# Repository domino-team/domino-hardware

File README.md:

This repository contains the Domino.IO hardware design files.

For further information, please check http://domino.io/

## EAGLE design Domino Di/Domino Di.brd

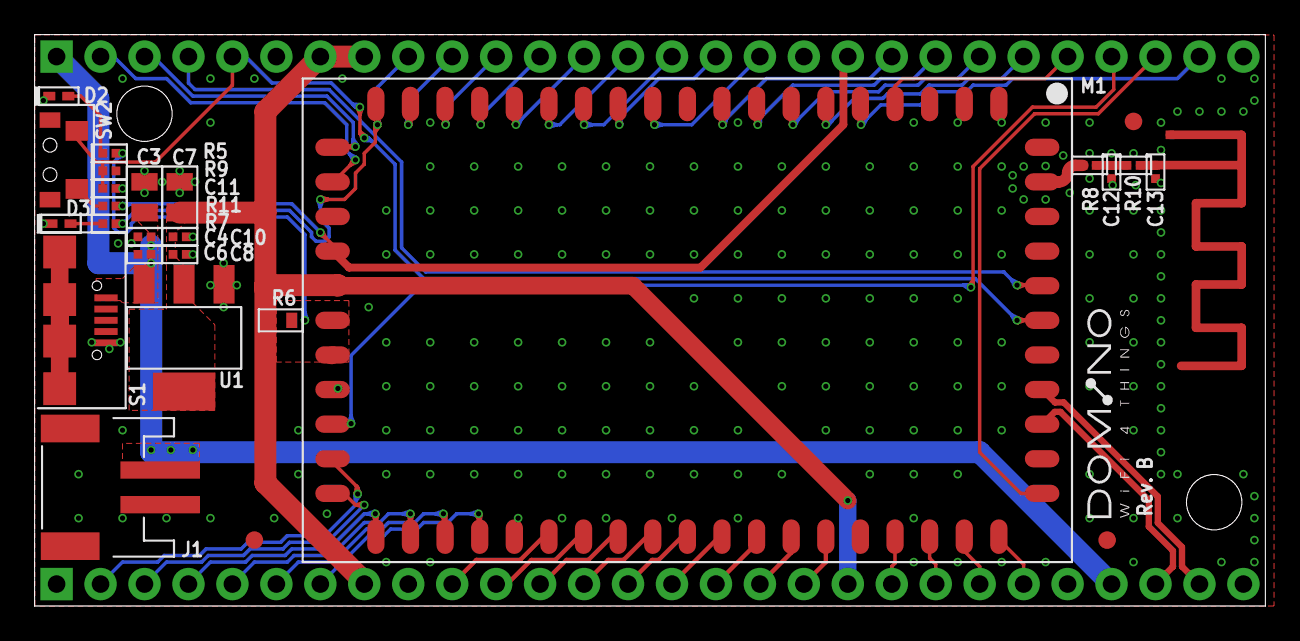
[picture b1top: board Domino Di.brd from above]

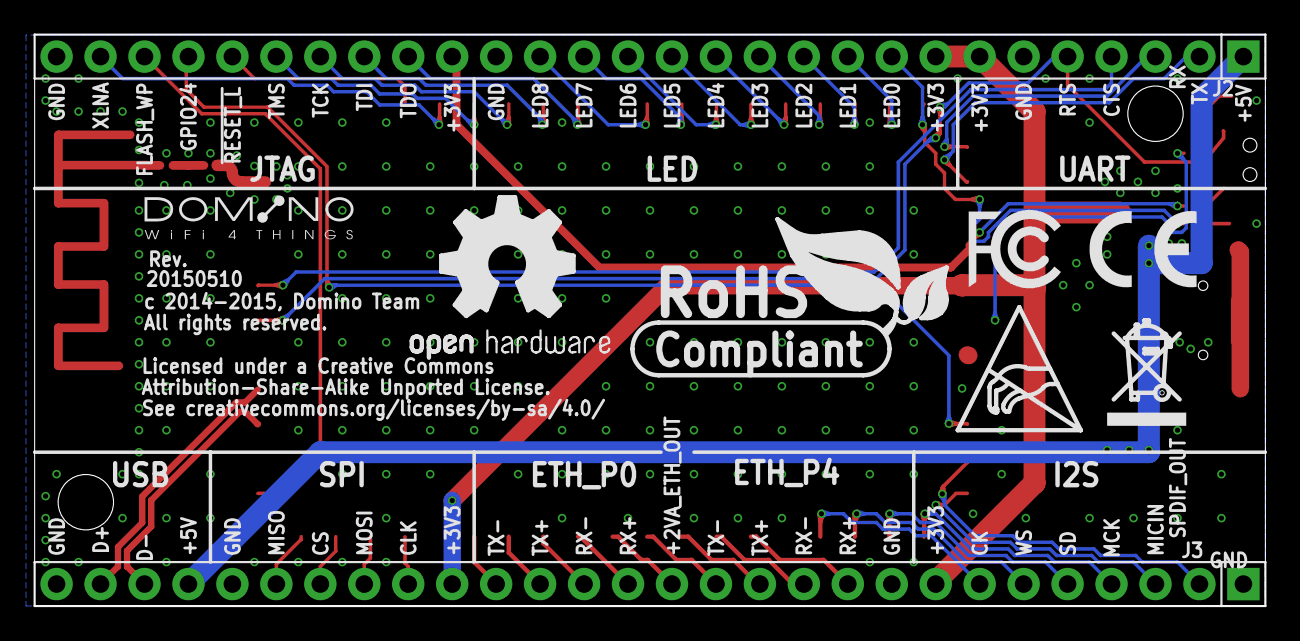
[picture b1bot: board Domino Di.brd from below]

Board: 2 copper layers, 71.1 x 33.0 mm, 41 parts (9 on the bottom side), 53 nets.

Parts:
A1: RF_ANT1
C3, C7: 22u; C0805
C4, C8: 10p; C0402
C6, C10: 100n; C0402
C11: 10n; C0402
C12, C13: DNP; C0402
CC-BY-SA: CC-BY-SA_LOGO
D2: RED; LED0402
D3: BLUE; LED0402
DRILEGEND: DRILEGEND
F1, F2, F3: FIDUCIAL
J1: LiPo Battery; S2B-PH-SM4-TB
J2, J3: MH28-1; MH28-1-0.1
M1: DOMINO
R5, R7: 270R; R0402
R6: 0R; R0603
R8, R10: 0R; R0402
R9: 10k; R0402
R11: 1k; R0402
S1: USB_MR5-001; USB-MR5-001
SW2: IT-1210
U1: AMS1117-3.3; SOT223
U$6, U$8: DOMINO_LOGO_SMALL
U$28: A5L-LOC
U$36: ESD_LOGO
U$38: OPEN_HARDWARE_LOGO
U$39: RECYCLE_BIN_LOGO
U$40: ROHS_LOGO
U$41: CE_LOGO_SMALL
U$42: FCC_LOGO_SMALL
W1: DOMINO_LOGO

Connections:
!RESET_L: J2.24, M1.4
+2V5: J2.19, M1.23, R11.2
+2VA_ETH_OUT: J3.14, M1.40
+3.3VD_IN: M1.25, M1.26, R5.2, R6.2
+3V3: C7.1, C8.1, C10.1, J2.7, J2.8, J3.8, J3.19, M1.24, R6.1, U1.2, U1.4
+5V: C3.1, C4.1, C6.1, J1.2, J2.1, J3.25, S1.1, U1.3
ANT0: M1.59, R8.1
ANT0_50R: A1.FEED, C13.1, R10.2
ANT0_EXT: C12.1, R8.2, R10.1
BLUE_LED: D3.2, R7.1
FLASH_WP: J2.26, M1.50
GND: A1.GND, C3.2, C4.2, C6.2, C7.2, C8.2, C10.2, C11.2, C12.2, C13.2, D2.1, D3.1, J1.1, J2.6, J2.18, J2.28, J3.1, J3.9, J3.24, J3.28, M1.1, M1.2, M1.3, M1.10, M1.22, M1.27, M1.35, M1.45, M1.51, M1.54, M1.57, M1.58, M1.60, R9.1, S1.5, S1.SH$1, S1.SH$2, S1.SH$3, S1.SH$4, SW2.SH$1, SW2.SH$2, U1.1
GPIO24: J2.25, M1.28
I2S_CK: J3.7, M1.34
I2S_MCK: J3.4, M1.31
I2S_MICIN: J3.3, M1.30
I2S_SD: J3.5, M1.32
I2S_WS: J3.6, M1.33
JTAG_TCK: J2.22, M1.7
JTAG_TDI: J2.21, M1.8
JTAG_TDO: J2.20, M1.9
JTAG_TMS: J2.23, M1.6
JUMPSTART: R11.1, SW2.1
LED0: J2.9, M1.19, R7.2
LED1: J2.10, M1.18
LED2: J2.11, M1.17
LED3: J2.12, M1.16
LED4: J2.13, M1.15
LED5: J2.14, M1.14
LED6: J2.15, M1.13
LED7: J2.16, M1.12
LED8: J2.17, M1.11
unnamed: D2.2, R5.1
P0_RX+: J3.15, M1.41
P0_RX-: J3.16, M1.42
P0_TX+: J3.17, M1.43
P0_TX-: J3.18, M1.44
P4_RX+: J3.10, M1.36
P4_RX-: J3.11, M1.37
P4_TX+: J3.12, M1.38
P4_TX-: J3.13, M1.39
SPDIF_OUT: J3.2, M1.29
SPI_CLK: J3.20, M1.46
SPI_CS: J3.22, M1.48
SPI_MISO: J3.23, M1.49
SPI_MOSI: J3.21, M1.47
UART_CTS: J2.4, M1.56
UART_RTS: C11.1, J2.5, M1.55, R9.2, SW2.2
UART_RX: J2.3, M1.20
UART_TX: J2.2, M1.21
USB_N: J3.26, M1.52
USB_P: J3.27, M1.53
XLNA: J2.27, M1.5

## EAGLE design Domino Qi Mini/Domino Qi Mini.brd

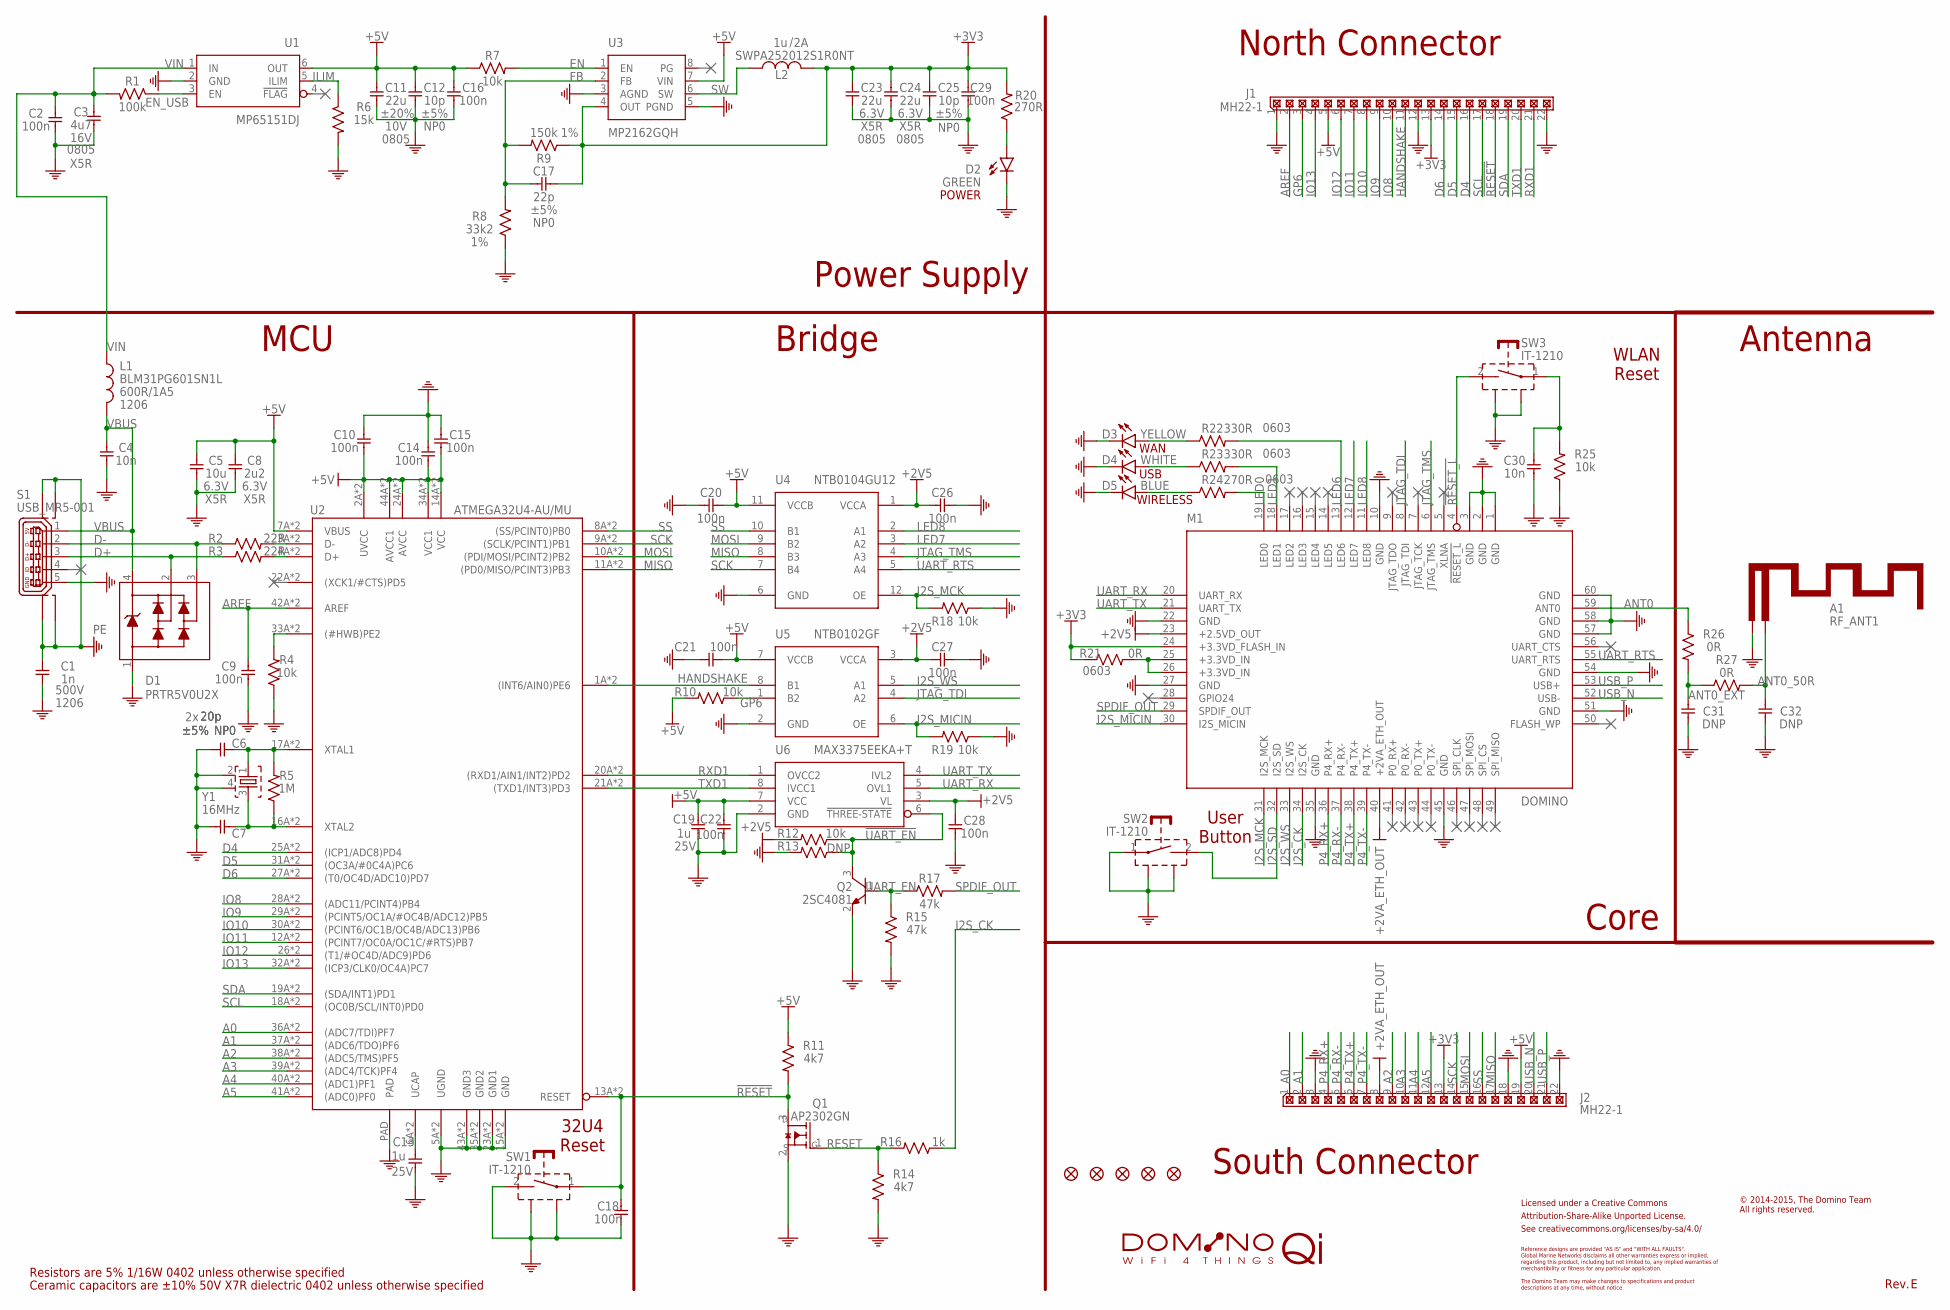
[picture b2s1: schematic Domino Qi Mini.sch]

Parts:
A1: RF_ANT1; PARTNO RF_ANT1
C1: 1n; C1206; PARTNO C1206_1n_X7R_10%_CER_500V
C2, C9, C10, C14, C15, C16, C18, C20, C21, C22, C26, C27, C28, C29: 100n; C0402; PARTNO C0402_100n_X7R_10%_CER_50V
C3: 4u7; C0805; PARTNO C0805_4u7_X5R_10%_CER_16V
C4, C30: 10n; C0402; PARTNO C0402_10n_X7R_10%_CER_50V
C5: 10u; C0402; PARTNO C0402_10u_X5R_10%_CER_6V3
C6, C7: 20p; C0402; PARTNO C0402_20p_NP0_5%_CER_50V
C8: 2u2; C0805; PARTNO C0402_2u2_X5R_10%_CER_6V3
C11: 22u; C0805; PARTNO C1206_22u_X7R_20%_CER_10V
C12, C25: 10p; C0402; PARTNO C0402_10p_NP0_5%_CER_50V
C13, C19: 1u; C0402; PARTNO C0402_1u_X7R_10%_CER_25V
C17: 22p; C0402; PARTNO C0402_22p_NP0_5%_CER_50V
C23, C24: 22u; C0805; PARTNO C0805_22u_X5R_20%_CER_6V3
C31, C32: DNP; C0402; PARTNO C0402_DNP
CC-BY-SA: CC-BY-SA_LOGO
D1: PRTR5V0U2X; SOT143B; PARTNO PRTR5V0U2X
D2: GREEN; LED0402; PARTNO LED0603-GREEN
D3: YELLOW; LED0402; PARTNO LED0603-YELLOW
D4: WHITE; LED0402; PARTNO LED0603-WHITE
D5: BLUE; LED0402; PARTNO LED0603-BLUE
F1, F2, F3, F4, F5: FIDUCIAL
J1, J2: MH22-1; MH22-1-0.1; PARTNO MH22-1-0.1
L1: BLM31PG601SN1L; FB1206; PARTNO BLM31PG601SN1L
L2: SWPA252012S1R0NT; SWPA252012S; PARTNO SWPA252012SMT
M1: DOMINO; PARTNO DOMINO-CORE
Q1: AP2302GN; SOT23-3; PARTNO AP2302GN
Q2: 2SC4081; SOT323; PARTNO 2SC4081
R1: 100k; R0402; PARTNO R0402_100k_5%_62.5mW
R2, R3: 22R; R0402; PARTNO R0402_22R_5%_62.5mW
R4, R7, R10, R12, R13, R18, R19, R25: 10k; R0402; PARTNO R0402_10k_5%_62.5mW
R5: 1M; R0402; PARTNO R0402_1M_5%_62.5mW
R6: 15k; R0402; PARTNO R0402_15k_5%_62.5mW
R8: 33k2; R0402; PARTNO R0402_33k2_1%_62.5mW
R9: 150k; R0402; PARTNO R0402_150k_1%_62.5mW
R11, R14: 4k7; R0402; PARTNO R0402_4k7_5%_62.5mW
R15, R17: 47k; R0402; PARTNO R0402_47k_5%_62.5mW
R16: 1k; R0402; PARTNO R0402_1k_5%_62.5mW
R20: 270R; R0402; PARTNO R0402_270R_5%_62.5mW
R21: 0R; R0603; PARTNO R0603_0R_5%_125mW
R22, R23: 330R; R0603; PARTNO R0603_330R_5%_125mW
R24: 270R; R0603; PARTNO R0603_270R_5%_125mW
R26, R27: 0R; R0402; PARTNO R0402_0R_5%_62.5mW
S1: USB_MR5-001; USB-MR5-001; PARTNO USB MR5-003A
SW1, SW2, SW3: IT-1210; PARTNO IT-1210
U1: MP65151DJ; SOT23-6; PARTNO MP65151DJ
U2: ATMEGA32U4-AU/MU; ATMEGA32U4_DUAL_FOOTPRINT; PARTNO ATMEGA32U4-MU
U3: MP2162GQH; QFN-8_2X1.5; PARTNO MP2162GQH
U4: NTB0104GU12; XQFN-12; PARTNO NTB0104GU12
U5: NTB0102GF; SOT1089; PARTNO NTB0102GF
U6: MAX3375EEKA+T; SOT23-8; PARTNO MAX3375EEKA+T
W1: DOMINO_QI_LOGO
Y1: 16MHz; CRYSTAL_32X25; PARTNO CRYSTAL_16MHZ_32X25_2SH_12PF_30PPM

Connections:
!RESET: C18.1, J1.18, Q1.3 (D), R11.2, SW1.1, U2.13A (RESET), U2.13M (RESET)
!RESET_L: M1.4 (!RESET_L), SW3.2
!UART_EN: Q2.3 (C), R12.1, R13.1, U6.6 (!THREE-STATE)
+2V5: C26.1, C27.1, C28.1, M1.23 (+2.5VD_OUT), R12.2, U4.1 (VCCA), U5.3 (VCCA), U6.3 (VL)
+2VA_ETH_OUT: J2.8, M1.40 (+2VA_ETH_OUT)
+3.3VD_IN: M1.25 (+3.3VD_IN), M1.26 (+3.3VD_IN), R21.2
+3V3: C17.2, C23.1, C24.1, C25.1, C29.1, J1.13, J2.13, L2.2, M1.24 (+3.3VD_FLASH_IN), R9.1, R20.2, R21.1, U3.4 (OUT)
+5V: C5.1, C8.1, C10.1, C11.1, C12.1, C14.1, C15.1, C16.1, C19.2, C20.1, C21.1, C22.1, J1.5, J2.19, R7.1, R10.2, R11.1, U1.6 (OUT), U2.2A (UVCC), U2.2M (UVCC), U2.7A (VBUS), U2.7M (VBUS), U2.14A (VCC), U2.14M (VCC), U2.24A (AVCC), U2.24M (AVCC), U2.34A (VCC1), U2.34M (VCC1), U2.44A (AVCC1), U2.44M (AVCC1), U3.7 (VIN), U4.11 (VCCB), U5.7 (VCCB), U6.7 (VCC)
A0: J2.1, U2.36A ((ADC7/TDI)PF7), U2.36M ((ADC7/TDI)PF7)
A1: J2.2, U2.37A ((ADC6/TDO)PF6), U2.37M ((ADC6/TDO)PF6)
A2: J2.9, U2.38A ((ADC5/TMS)PF5), U2.38M ((ADC5/TMS)PF5)
A3: J2.10, U2.39A ((ADC4/TCK)PF4), U2.39M ((ADC4/TCK)PF4)
A4: J2.11, U2.40A ((ADC1)PF1), U2.40M ((ADC1)PF1)
A5: J2.12, U2.41A ((ADC0)PF0), U2.41M ((ADC0)PF0)
ANT0: M1.59 (ANT0), R26.1
ANT0_50R: A1.FEED, C32.1, R27.2
ANT0_EXT: C31.1, R26.2, R27.1
AREF: C9.1, J1.2, U2.42A (AREF), U2.42M (AREF)
BLUE_LED: D5.2 (A), R24.1
BLUE_LED1: D4.2 (A), R23.1
BLUE_LED2: D3.2 (A), R22.1
D4: J1.16, U2.25A ((ICP1/ADC8)PD4), U2.25M ((ICP1/ADC8)PD4)
D5: J1.15, U2.31A ((OC3A/#0C4A)PC6), U2.31M ((OC3A/#0C4A)PC6)
D6: J1.14, U2.27A ((T0/OC4D/ADC10)PD7), U2.27M ((T0/OC4D/ADC10)PD7)
D+: D1.2, R3.1, S1.3
D-: D1.3, R2.1, S1.2
EN: R7.2, U3.1 (EN)
EN_USB: R1.1, U1.3 (EN)
FB: C17.1, R8.2, R9.2, U3.2 (FB)
GND: A1.GND, C1.2, C2.2, C3.2, C4.2, C5.2, C6.1, C7.1, C8.2, C9.2, C10.2, C11.2, C12.2, C13.1, C14.2, C15.2, C16.2, C18.2, C19.1, C20.2, C21.2, C22.2, C23.2, C24.2, C25.2, C26.2, C27.2, C28.2, C29.2, C30.2, C31.2, C32.2, D1.1, D2.1 (C), D3.1 (C), D4.1 (C), D5.1 (C), J1.1, J1.12, J1.22, J2.3, J2.18, J2.22, M1.1 (GND), M1.2 (GND), M1.3 (GND), M1.10 (GND), M1.22 (GND), M1.27 (GND), M1.35 (GND), M1.45 (GND), M1.51 (GND), M1.54 (GND), M1.57 (GND), M1.58 (GND), M1.60 (GND), Q1.2 (S), Q2.2 (E), R4.1, R6.2, R8.1, R13.2, R14.2, R15.2, R18.1, R19.1, R25.1, S1.5, SW1.2, SW1.SH$1, SW1.SH$2, SW2.1, SW2.SH$1, SW2.SH$2, SW3.SH$1, SW3.SH$2, U1.2 (GND), U2.5A (UGND), U2.5M (UGND), U2.15A (GND), U2.15M (GND), U2.23A (GND1), U2.23M (GND1), U2.35A (GND2), U2.35M (GND2), U2.43A (GND3), U2.43M (GND3), U2.PAD, U3.3 (AGND), U3.5 (PGND), U4.6 (GND), U5.2 (GND), U6.2 (GND), Y1.2, Y1.4
GP6: J1.3, R10.1, U5.1 (B2)
HANDSHAKE: J1.11, U2.1A ((INT6/AIN0)PE6), U2.1M ((INT6/AIN0)PE6), U5.8 (B1)
I2S_CK: M1.34 (I2S_CK), R16.1
I2S_MCK: M1.31 (I2S_MCK), R18.2, U4.12 (OE)
I2S_MICIN: M1.30 (I2S_MICIN), R19.2, U5.6 (OE)
I2S_SD: M1.32 (I2S_SD), SW2.2
I2S_WS: M1.33 (I2S_WS), U5.5 (A1)
ILIM: R6.1, U1.5 (ILIM)
IO8: J1.10, U2.28A ((ADC11/PCINT4)PB4), U2.28M ((ADC11/PCINT4)PB4)
IO9: J1.9, U2.29A ((PCINT5/OC1A/#OC4B/ADC12)PB5), U2.29M ((PCINT5/OC1A/#OC4B/ADC12)PB5)
IO10: J1.8, U2.30A ((PCINT6/OC1B/OC4B/ADC13)PB6), U2.30M ((PCINT6/OC1B/OC4B/ADC13)PB6)
IO11: J1.7, U2.12A ((PCINT7/OC0A/OC1C/#RTS)PB7), U2.12M ((PCINT7/OC0A/OC1C/#RTS)PB7)
IO12: J1.6, U2.26 ((T1/#OC4D/ADC9)PD6), U2.26M ((T1/#OC4D/ADC9)PD6)
IO13: J1.4, U2.32A ((ICP3/CLK0/OC4A)PC7), U2.32M ((ICP3/CLK0/OC4A)PC7)
JTAG_TDI: M1.8 (JTAG_TDI), U5.4 (A2)
JTAG_TMS: M1.6 (JTAG_TMS), U4.4 (A3)
LED0: M1.19 (LED0), R24.2
LED1: M1.18 (LED1), R23.2
LED6: M1.13 (LED6), R22.2
LED7: M1.12 (LED7), U4.3 (A2)
LED8: M1.11 (LED8), U4.2 (A1)
MISO: J2.17, U2.11A ((PD0/MISO/PCINT3)PB3), U2.11M ((PD0/MISO/PCINT3)PB3), U4.8 (B3)
MOSI: J2.15, U2.10A ((PDI/MOSI/PCINT2)PB2), U2.10M ((PDI/MOSI/PCINT2)PB2), U4.9 (B2)
unnamed: R2.2, U2.3A (D-), U2.3M (D-)
unnamed: R4.2, U2.33A ((#HWB)PE2), U2.33M ((#HWB)PE2)
unnamed: R3.2, U2.4A (D+), U2.4M (D+)
P4_RX+: J2.4, M1.36 (P4_RX+)
P4_RX-: J2.5, M1.37 (P4_RX-)
P4_TX+: J2.6, M1.38 (P4_TX+)
P4_TX-: J2.7, M1.39 (P4_TX-)
PE: C1.1, S1.SH$1 (M0), S1.SH$2 (M1), S1.SH$3 (M2), S1.SH$4 (M3)
POWER_LED: D2.2 (A), R20.1
RESET: Q1.1 (G), R14.1, R16.2
RESET_SWITCH: C30.1, R25.2, SW3.1
RXD1: J1.21, U2.20A ((RXD1/AIN1/INT2)PD2), U2.20M ((RXD1/AIN1/INT2)PD2), U6.1 (OVCC2)
SCK: J2.14, U2.9A ((SCLK/PCINT1)PB1), U2.9M ((SCLK/PCINT1)PB1), U4.7 (B4)
SCL: J1.17, U2.18A ((OC0B/SCL/INT0)PD0), U2.18M ((OC0B/SCL/INT0)PD0)
SDA: J1.19, U2.19A ((SDA/INT1)PD1), U2.19M ((SDA/INT1)PD1)
SPDIF_OUT: M1.29 (SPDIF_OUT), R17.2
SS: J2.16, U2.8A ((SS/PCINT0)PB0), U2.8M ((SS/PCINT0)PB0), U4.10 (B1)
SW: L2.1, U3.6 (SW)
TXD1: J1.20, U2.21A ((TXD1/INT3)PD3), U2.21M ((TXD1/INT3)PD3), U6.8 (IVCC1)
UART_EN: Q2.1 (B), R15.1, R17.1
UART_RTS: M1.55 (UART_RTS), U4.5 (A4)
UART_RX: M1.20 (UART_RX), U6.5 (OVL1)
UART_TX: M1.21 (UART_TX), U6.4 (IVL2)
UCAP: C13.2, U2.6A (UCAP), U2.6M (UCAP)
USB_N: J2.20, M1.52 (USB-)
USB_P: J2.21, M1.53 (USB+)
VBUS: C4.1, D1.4, L1.2, S1.1
VIN: C2.1, C3.1, L1.1, R1.2, U1.1 (IN)
XTAL1: C6.2, R5.2, U2.17A (XTAL1), U2.17M (XTAL1), Y1.1
XTAL2: C7.2, R5.1, U2.16A (XTAL2), U2.16M (XTAL2), Y1.3

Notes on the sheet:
Power Supply
North Connector
South Connector
Antenna
Core
MCU
Ceramic capacitors are ±10% 50V X7R dielectric 0402 unless otherwise specified
Resistors are 5% 1/16W 0402 unless otherwise specified
Licensed under a Creative Commons
Attribution-Share-Alike Unported License.
See creativecommons.org/licenses/by-sa/4.0/
Reference designs are provided "AS IS" and "WITH ALL FAULTS".
regarding this product, including but not limited to, any implied warranties of
The Domino Team may make changes to specifications and product
Global Marine Networks disclaims all other warranties express or implied,
merchantibility or fitness for any particular application.
descriptions at any time, without notice.
© 2014-2015, The Domino Team All rights reserved.
Rev.
WIRELESS
POWER
Bridge
32U4 Reset
USB
WAN
User Button
WLAN Reset

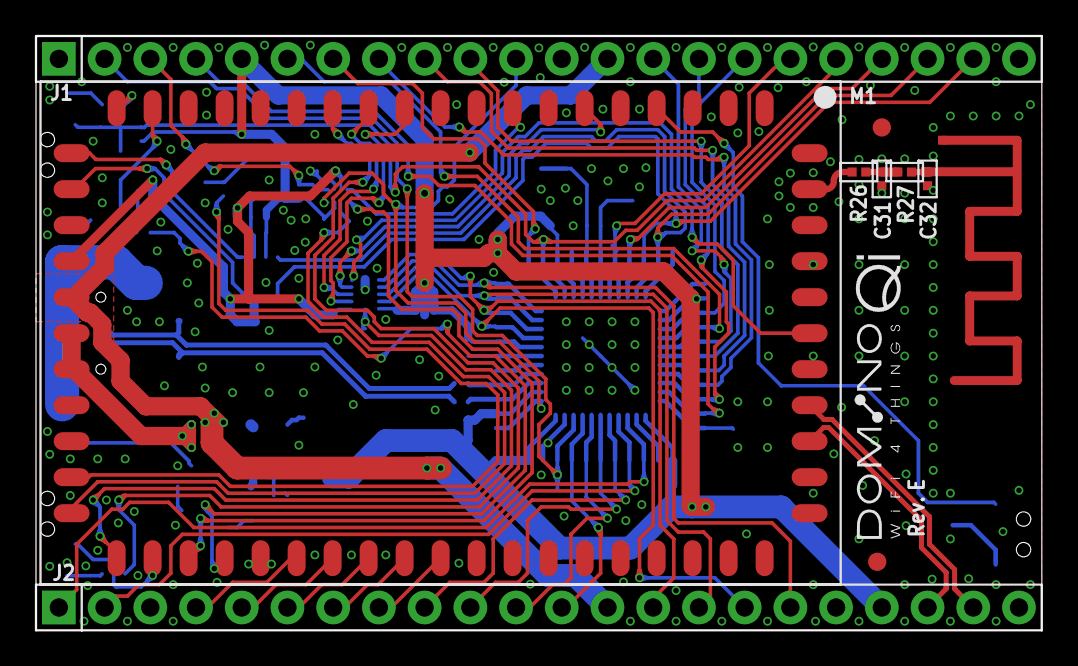
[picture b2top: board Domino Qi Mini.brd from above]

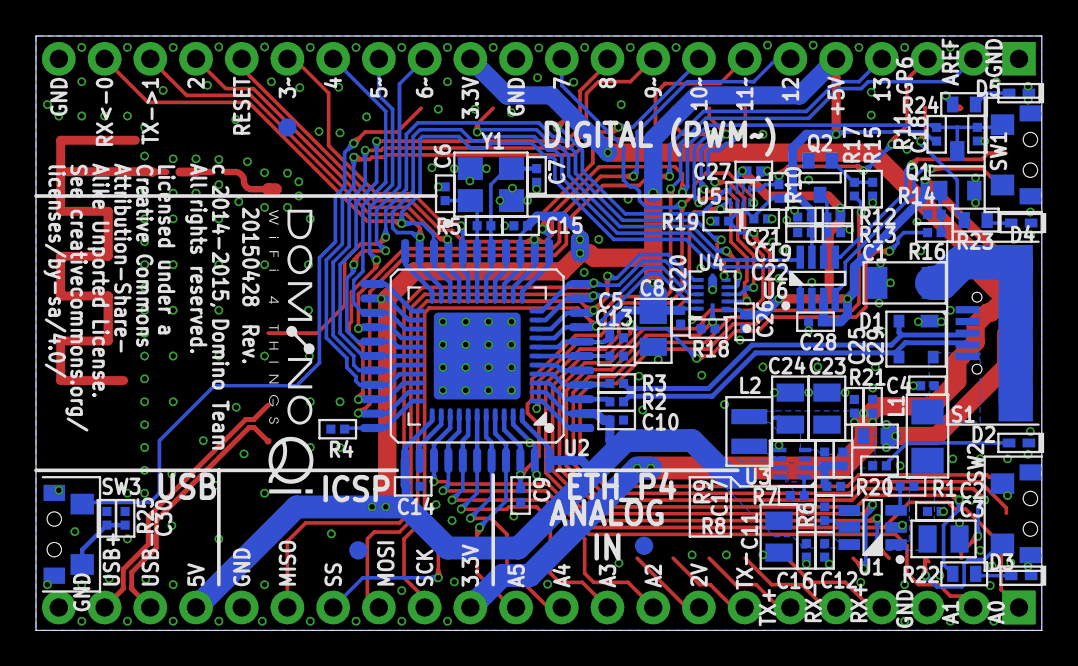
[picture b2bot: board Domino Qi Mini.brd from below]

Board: 4 copper layers, 55.9 x 33.0 mm, 94 parts (79 on the bottom side), 83 nets.

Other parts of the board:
DRILEGEND: DRILEGEND
U$3, U$5: DOMINO_QI_LOGO_SMALL
U$28: A5L-LOC

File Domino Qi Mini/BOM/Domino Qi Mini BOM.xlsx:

Item | Qty | Value | Manufacturer | Device | Package | Reference | Description | Remarks
1 | 1 | 1n | ANY | C1206_1n_X7R_10%_CER_500V | C1206 | C1 | CAP CER 1000PF 500V 10% X7R 1206
2 | 1 | 22u | ANY | C1206_22u_X7R_20%_CER_10V | C0805 | C11 | CAP CER 22UF 10V 20% X7R 1206
3 | 2 | 10p | ANY | C0402_10p_NP0_5%_CER_50V | C0402 | C12, C25 | CAP CER 10PF 50V 5% NP0 0402
4 | 2 | 1u | ANY | C0402_1u_X7R_10%_CER_25V | C0402 | C13, C19 | CAP CER 1UF 25V 10% X7R 0402
5 | 1 | 22p | ANY | C0402_22p_NP0_5%_CER_50V | C0402 | C17 | CAP CER 22PF 50V 5% NP0 0402
6 | 14 | 100n | ANY | C0402_100n_X7R_10%_CER_50V | C0402 | C2, C9, C10, C14, C15, C16, C18, C20, C21, C22, C26, C27, C28, C29 | CAP CER 0.1UF 50V 10% X7R 0402
7 | 2 | 22u | ANY | C0805_22u_X5R_20%_CER_6V3 | C0805 | C23, C24 | CAP CER 22UF 6.3V 20% X5R 0805
8 | 1 | 4u7 | ANY | C0805_4u7_X5R_10%_CER_16V | C0805 | C3 | CAP CER 4.7UF 16V 10% X5R 0805
9 | 0 | DNP | NONE | C0402_DNP | C0402 | C31(DNP), C32(DNP) | CAP DNP 0402
10 | 2 | 10n | ANY | C0402_10n_X7R_10%_CER_50V | C0402 | C4, C30 | CAP CER 10000PF 50V 10% X7R 0402
11 | 1 | 10u | ANY | C0402_10u_X5R_10%_CER_6V3 | C0402 | C5 | CAP CER 10UF 6.3V 10% X5R 0402
12 | 2 | 20p | ANY | C0402_20p_NP0_5%_CER_50V | C0402 | C6, C7 | CAP CER 20PF 50V 5% NP0 0402
13 | 1 | 2u2 | ANY | C0402_2u2_X5R_10%_CER_6V3 | C0805 | C8 | CAP CER 2.2UF 6.3V 20% X5R 0402
14 | 1 | PRTR5V0U2X | NXP | PRTR5V0U2X | SOT143B | D1 | TVS DIODE ARRAY 2CH 5V SOT143
15 | 1 | GREEN | ANY | LED0603-GREEN | LED0402 | D2 | LED GREEN CLEAR 0603 SMD
16 | 1 | YELLOW | ANY | LED0603-YELLOW | LED0402 | D3 | LED YELLOW CLEAR 0603 SMD
17 | 1 | WHITE | ANY | LED0603-WHITE | LED0402 | D4 | LED WHITE CLEAR 0603 SMD
18 | 1 | BLUE | ANY | LED0603-BLUE | LED0402 | D5 | LED BLUE CLEAR 0603 SMD
19 | 2 | MH22-1 | ANY | MH22-1-0.1 | MH22-1-0.1 | J1, J2 | CONN HEADER VERT .100 1ROW 22POS 10.5 TAIL 8.5 BODY 15AU
20 | 1 | BLM31PG601SN1L | MURATA | BLM31PG601SN1L | FB1206 | L1 | FERRITE CHIP 600 OHM 1500MA 1206
21 | 1 | SWPA252012S1R0NT | SUNLORD | SWPA252012SMT | SWPA252012S | L2 | INDUCTOR 1.2UH 2.0A SMD2.5 X 2.0 X 1.2
22 | 1 | DOMINO | GL-CONNECT | DOMINO-CORE | DOMINO | M1 | MOD AR9331 WIFI
23 | 1 | AP2302GN | ANPEC | AP2302GN | SOT23-3 | Q1 | MOSFET N-CH 20V 2.8A SOT-23
24 | 1 | 2SC4081 | ROHM SEMICONDUCTOR | 2SC4081 | SOT323 | Q2 | TRANS NPN 50V 0.15A SOT-323
25 | 1 | 100k | ANY | R0402_100k_5%_62.5mW | R0402 | R1 | RES 100K OHM 1/16W 5% 0402 SMD
26 | 2 | 4k7 | ANY | R0402_4k7_5%_62.5mW | R0402 | R11, R14 | RES 4.7K OHM 1/16W 5% 0402 SMD
27 | 2 | 47k | ANY | R0402_47k_5%_62.5mW | R0402 | R15, R17 | RES 47K OHM 1/16W 5% 0402 SMD
28 | 1 | 1k | ANY | R0402_1k_5%_62.5mW | R0402 | R16 | RES 1K OHM 1/16W 5% 0402 SMD
29 | 2 | 22R | ANY | R0402_22R_5%_62.5mW | R0402 | R2, R3 | RES 22 OHM 1/16W 5% 0402 SMD
30 | 1 | 270R | ANY | R0402_270R_5%_62.5mW | R0402 | R20 | RES 270 OHM 1/16W 5% 0402 SMD
31 | 1 | 0R | ANY | R0603_0R_5%_125mW | R0603 | R21 | RES 0.0 OHM 1/8W JUMP SMD 0603
32 | 2 | 330R | ANY | R0603_330R_5%_125mW | R0603 | R22, R23 | RES 330 OHM 1/8W 5% 0603 SMD
33 | 1 | 270R | ANY | R0603_270R_5%_125mW | R0603 | R24 | RES 270 OHM 1/8W 5% 0603 SMD
34 | 2 | 0R | ANY | R0402_0R_5%_62.5mW | R0402 | R26, R27 | RES 0.0 OHM 1/16W JUMP 0402 SMD
35 | 7 | 10k | ANY | R0402_10k_5%_62.5mW | R0402 | R4, R7, R10, R12, R13(DNP), R18, R19, R25 | RES 10K OHM 1/16W 5% 0402 SMD
36 | 1 | 1M | ANY | R0402_1M_5%_62.5mW | R0402 | R5 | RES 1M OHM 1/16W 0402 SMD
37 | 1 | 15k | ANY | R0402_15k_5%_62.5mW | R0402 | R6 | RES 15K OHM 1/16W 5% 0402 SMD
38 | 1 | 33k2 | ANY | R0402_33k2_1%_62.5mW | R0402 | R8 | RES 33.2K OHM 1/16W 1% 0402 SMD
39 | 1 | 150k | ANY | R0402_150k_1%_62.5mW | R0402 | R9 | RES 150K OHM 1/16W 1% 0402 SMD
40 | 1 | USB_MR5-001 | SZJUSTWELL ELECTRONICS | USB MR5-003A | USB-MR5-001 | S1 | CONN USB MICRO B RECPT SMT R/A
41 | 3 | IT-1210 | SZJUSTWELL ELECTRONICS | IT-1210 | IT-1210 | SW1, SW2, SW3 | SWITCH TACTILE SPST-NO 0.05A 12V
42 | 1 | MP65151DJ | MONOLITHIC POWER | MP65151DJ | SOT23-6 | U1 | IC POWER SWITCH 1.7A SOT23-6
43 | 1 | ATMEGA32U4-AU/MU | ATMEL | ATMEGA32U4-MU | ATMEGA32U4_DUAL_FOOTPRINT | U2 | IC MCU 8BIT 32KB FLASH 44QFN | Or ATMEGA32U4-AU
44 | 1 | MP2162GQH | MONOLITHIC POWER | MP2162GQH | QFN-8_2X1.5 | U3 | IC REG BUCK SYNC ADJ 2A 8WDFN
45 | 1 | NTB0104GU12 | NXP | NTB0104GU12 | XQFN-12 | U4 | IC TRANSLATING TXRX 12XQFN
46 | 1 | NTB0102GF | NXP | NTB0102GF | SOT1089 | U5 | TXRX TRANSLATING DUAL 3ST 8XSON
47 | 1 | MAX3375EEKA+T | MAXIM INTEGRATED | MAX3375EEKA+T | SOT23-8 | U6 | IC LVL XLTR LV 8MBPS SOT23-8
48 | 1 | 16MHz | ANY | CRYSTAL_16MHZ_32X25_2SH_12PF_30PPM | CRYSTAL_32X25 | Y1 | CRYSTAL 16MHZ 12PF 30PPM 3.2 X 2.5 SMD

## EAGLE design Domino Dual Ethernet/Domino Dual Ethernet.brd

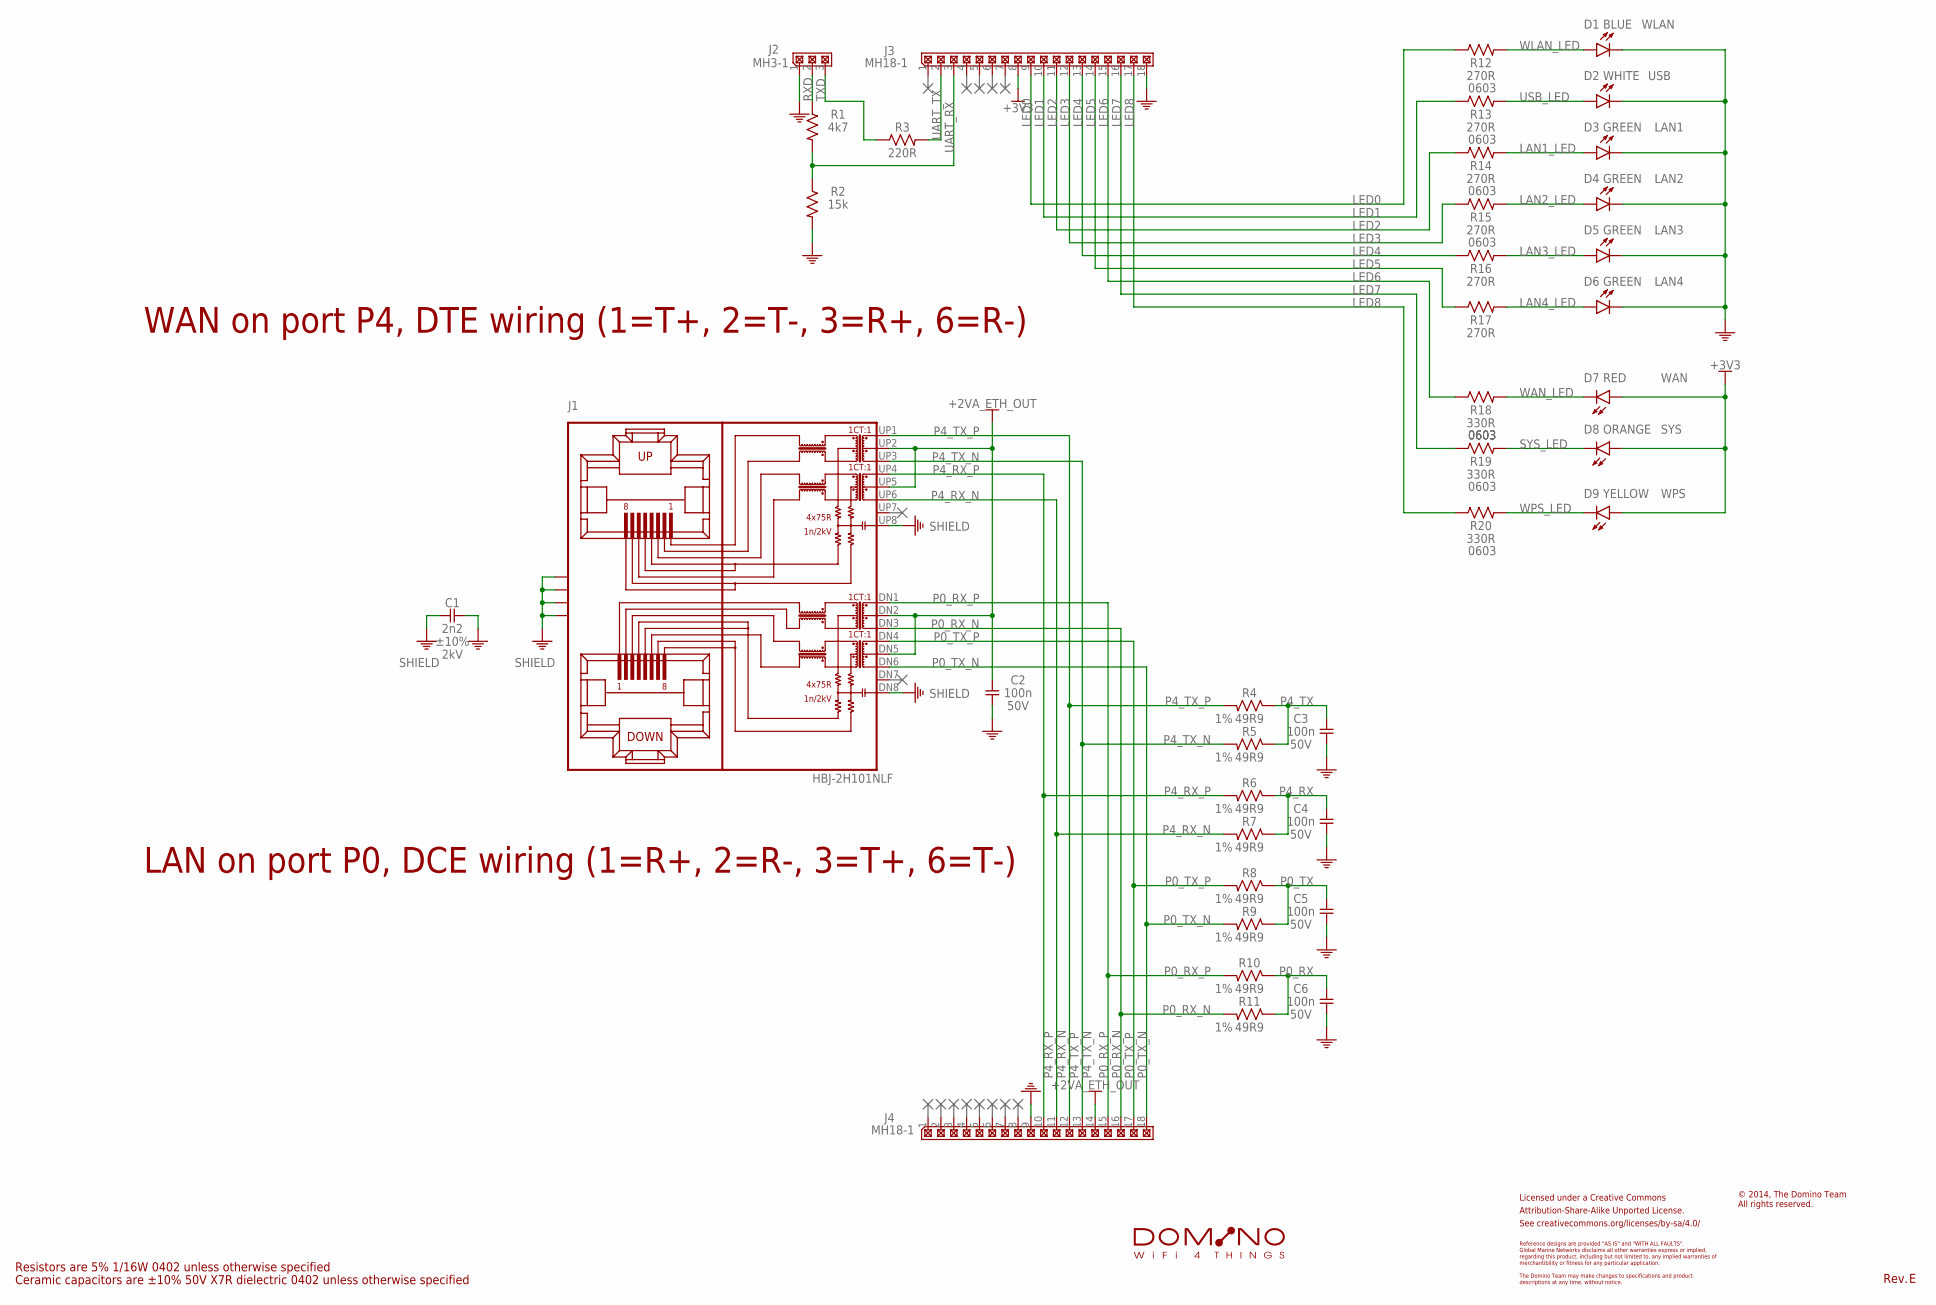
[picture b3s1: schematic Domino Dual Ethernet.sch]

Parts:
C1: 2n2; C1206; PARTNO C1210_2n2_X7R_10%_CER_2kV
C2, C3, C4, C5, C6: 100n; C0402; PARTNO C0402_100n_X7R_10%_CER_50V
CC-BY-SA1: CC-BY-SA_LOGO
D1: BLUE; LED0603; PARTNO LED0603-BLUE
D2: WHITE; LED0603; PARTNO LED0603-WHITE
D3, D4, D5, D6: GREEN; LED0603; PARTNO LED0603-GREEN
D7: RED; LED0603; PARTNO LED0603-ORANGE
D8: ORANGE; LED0603; PARTNO LED0603-ORANGE
D9: YELLOW; LED0603; PARTNO LED0603-YELLOW
J1: HBJ-2H101NLF; PARTNO HBJ-2H101NLF
J2: MH3-1; MH3-1-0.1; PARTNO MH3-1-0.1
J3, J4: MH18-1; MH18-1-0.1; PARTNO MH18-1-0.1
L1: DOMINO_LOGO
R1: 4k7; R0402; PARTNO R0402_4k7_5%_62.5mW
R2: 15k; R0402; PARTNO R0402_15k_5%_62.5mW
R3: 220R; R0402; PARTNO R0402_220R_5%_62.5mW
R4, R5, R6, R7, R8, R9, R10, R11: 49R9; R0402; PARTNO R0402_49R9_1%_62.5mW
R12, R13, R14, R15, R16, R17: 270R; R0603; PARTNO R0603_270R_5%_125mW
R18, R19, R20: 330R; R0603; PARTNO R0603_330R_5%_125mW

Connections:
+2VA_ETH_OUT: C2.2, J1.DN2 (DR2), J1.DN5 (DR5), J1.UP2 (UR2), J1.UP5 (UR5), J4.14
+3V3: D7.2 (A), D8.2 (A), D9.2 (A), J3.8
GND: C1.1, C2.1, C3.1, C4.1, C5.1, C6.1, D1.1 (C), D2.1 (C), D3.1 (C), D4.1 (C), D5.1 (C), D6.1 (C), J2.1, J3.18, J4.9, R2.2
LAN1_LED: D3.2 (A), R14.2
LAN2_LED: D4.2 (A), R15.2
LAN3_LED: D5.2 (A), R16.2
LAN4_LED: D6.2 (A), R17.2
LED0: J3.9, R12.1
LED1: J3.10, R13.1
LED2: J3.11, R14.1
LED3: J3.12, R15.1
LED4: J3.13, R16.1
LED5: J3.14, R17.1
LED6: J3.15, R18.1
LED7: J3.16, R19.1
LED8: J3.17, R20.1
P0_RX: C6.2, R10.1, R11.1
P0_RX_N: J1.DN3 (DR3), J4.16, R11.2
P0_RX_P: J1.DN1 (DR1), J4.15, R10.2
P0_TX: C5.2, R8.1, R9.1
P0_TX_N: J1.DN6 (DR6), J4.18, R9.2
P0_TX_P: J1.DN4 (DR4), J4.17, R8.2
P4_RX: C4.2, R6.1, R7.1
P4_RX_N: J1.UP6 (UR6), J4.11, R7.2
P4_RX_P: J1.UP4 (UR4), J4.10, R6.2
P4_TX: C3.2, R4.1, R5.1
P4_TX_N: J1.UP3 (UR3), J4.13, R5.2
P4_TX_P: J1.UP1 (UR1), J4.12, R4.2
RXD: J2.2, R1.1
SHIELD: C1.2, J1.DN8 (DR8), J1.P$1 (SHIELD), J1.P$2 (SHIELD), J1.P$3 (SHIELD), J1.P$4 (SHIELD), J1.UP8 (UR8)
SYS_LED: D8.1 (C), R19.2
TXD: J2.3, R3.1
UART_RX: J3.3, R1.2, R2.1
UART_TX: J3.2, R3.2
USB_LED: D2.2 (A), R13.2
WAN_LED: D7.1 (C), R18.2
WLAN_LED: D1.2 (A), R12.2
WPS_LED: D9.1 (C), R20.2

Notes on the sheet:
Ceramic capacitors are ±10% 50V X7R dielectric 0402 unless otherwise specified
Resistors are 5% 1/16W 0402 unless otherwise specified
Licensed under a Creative Commons
Attribution-Share-Alike Unported License.
See creativecommons.org/licenses/by-sa/4.0/
Reference designs are provided "AS IS" and "WITH ALL FAULTS".
regarding this product, including but not limited to, any implied warranties of
The Domino Team may make changes to specifications and product
Global Marine Networks disclaims all other warranties express or implied,
merchantibility or fitness for any particular application.
descriptions at any time, without notice.
© 2014, The Domino Team All rights reserved.
Rev.
WAN on port P4, DTE wiring (1=T+, 2=T-, 3=R+, 6=R-)
WLAN
USB
LAN1
LAN2
LAN3
LAN4
SYS
WPS
WAN
LAN on port P0, DCE wiring (1=R+, 2=R-, 3=T+, 6=T-)

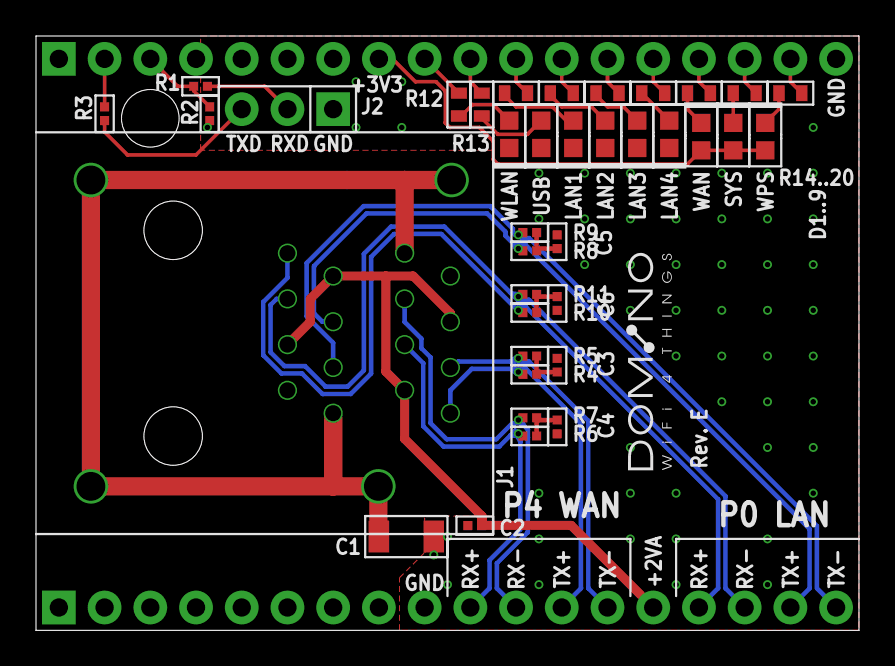
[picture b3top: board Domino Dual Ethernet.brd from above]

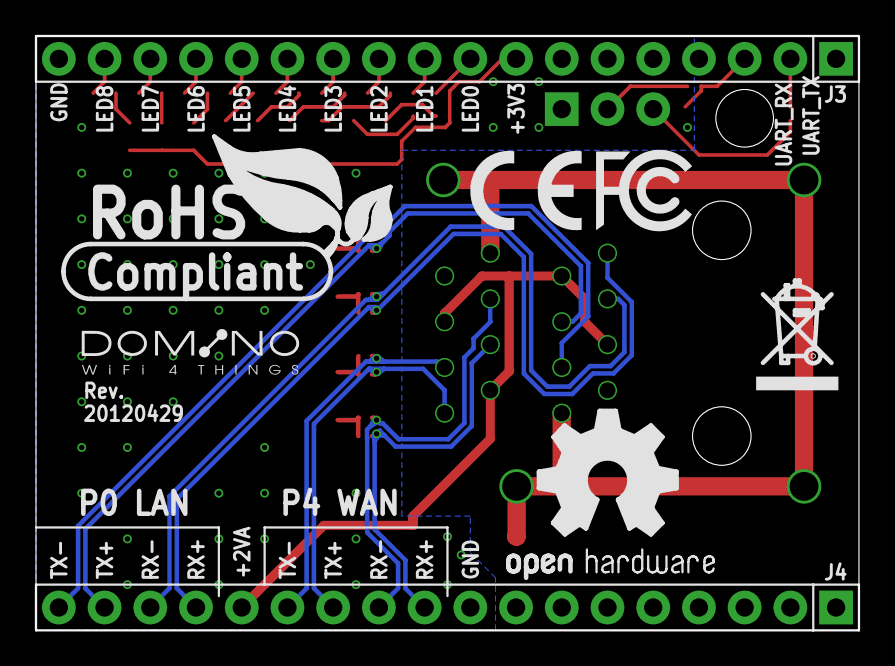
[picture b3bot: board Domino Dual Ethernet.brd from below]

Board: 2 copper layers, 45.7 x 33.0 mm, 50 parts (8 on the bottom side), 38 nets.

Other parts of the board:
DRILEGEND: DRILEGEND
U$3: A5L-LOC
U$4, U$11: DOMINO_LOGO_SMALL
U$5: CE_LOGO_SMALL
U$6: FCC_LOGO_SMALL
U$7: OPEN_HARDWARE_LOGO
U$8: RECYCLE_BIN_LOGO
U$9: ROHS_LOGO

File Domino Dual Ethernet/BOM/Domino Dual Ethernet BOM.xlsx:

Item | Qty | Value | Manufacturer | Device | Package | Reference | Description | Remarks
1 | 1 | 2n2 | ANY | C1210_2n2_X7R_10%_CER_2kV | C1206 | C1 | CAP CER 2200PF 1KV 10% X7R 1210
2 | 5 | 100n | ANY | C0402_100n_X7R_10%_CER_50V | C0402 | C2, C3, C4, C5, C6 | CAP CER 0.1UF 50V 10% X7R 0402
3 | 1 | BLUE | ANY | LED0603-BLUE | LED0603 | D1 | LED BLUE CLEAR 0603 SMD
4 | 1 | WHITE | ANY | LED0603-WHITE | LED0603 | D2 | LED WHITE CLEAR 0603 SMD
5 | 4 | GREEN | ANY | LED0603-GREEN | LED0603 | D3, D4, D5, D6 | LED GREEN CLEAR 0603 SMD
6 | 1 | RED | ANY | LED0603-ORANGE | LED0603 | D7 | LED ORANGE CLEAR 0603 SMD
7 | 1 | ORANGE | ANY | LED0603-ORANGE | LED0603 | D8 | LED ORANGE CLEAR 0603 SMD
8 | 1 | YELLOW | ANY | LED0603-YELLOW | LED0603 | D9 | LED YELLOW CLEAR 0603 SMD
9 | 1 | HBJ-2H101NLF | SHEZHEN HUILY ELECTRONICS | HBJ-2H101NLF | HBJ-2H101NLF | J1 | CONN MAGJACK 2PORT 100 BASE-T
10 | 1 | MH3-1 | ANY | MH3-1-0.1 | MH3-1-0.1 | J2 | CONN HEADER VERT .100 1ROW 3POS 8.08 HEAD 3.05 TAIL 15AU
11 | 2 | MH18-1 | ANY | MH18-1-0.1 | MH18-1-0.1 | J3, J4 | CONN HEADER VERT .100 1ROW 18POS 8.08 HEAD 3.05 TAIL 15AU
12 | 1 | 4k7 | ANY | R0402_4k7_5%_62.5mW | R0402 | R1 | RES 4.7K OHM 1/16W 5% 0402 SMD
13 | 6 | 270R | ANY | R0603_270R_5%_125mW | R0603 | R12, R13, R14, R15, R16, R17 | RES 270 OHM 1/8W 5% 0603 SMD
14 | 3 | 330R | ANY | R0603_330R_5%_125mW | R0603 | R18, R19, R20 | RES 330 OHM 1/8W 5% 0603 SMD
15 | 1 | 15k | ANY | R0402_15k_5%_62.5mW | R0402 | R2 | RES 15K OHM 1/16W 5% 0402 SMD
16 | 1 | 220R | ANY | R0402_220R_5%_62.5mW | R0402 | R3 | RES 220 OHM 1/16W 5% 0402 SMD
17 | 8 | 49R9 | ANY | R0402_49R9_1%_62.5mW | R0402 | R4, R5, R6, R7, R8, R9, R10, R11 | RES 49.9 OHM 1/16W 1% 0402 SMD

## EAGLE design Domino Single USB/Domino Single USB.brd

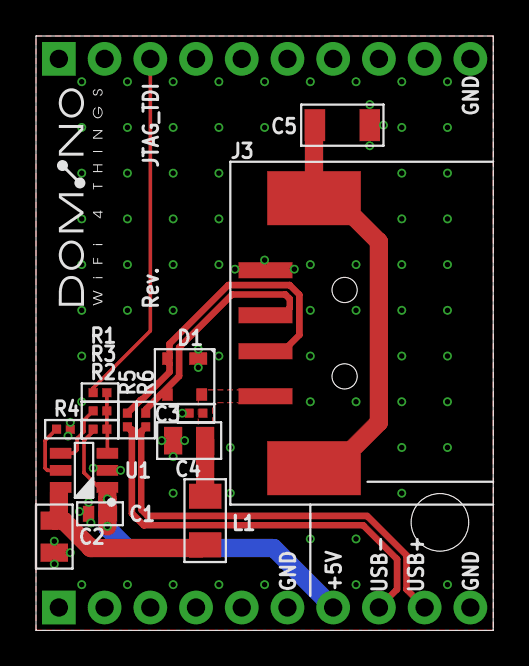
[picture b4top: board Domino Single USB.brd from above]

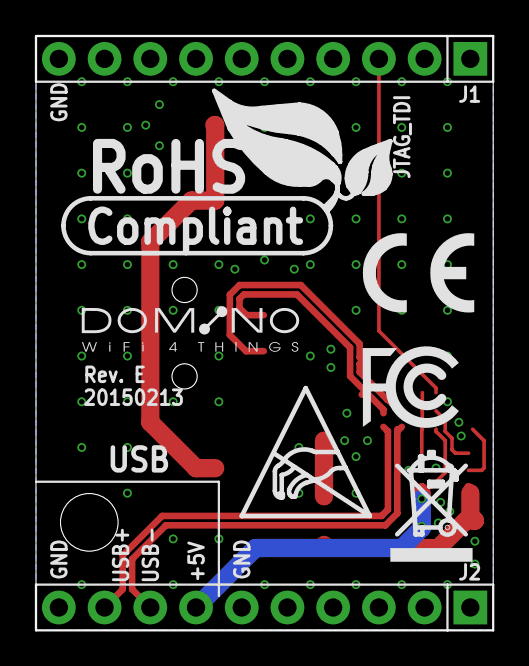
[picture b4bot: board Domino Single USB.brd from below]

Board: 2 copper layers, 25.4 x 33.0 mm, 28 parts (8 on the bottom side), 13 nets.

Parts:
C1: 10u; C0603
C2: 22u; C0805
C3: 100n; C0402
C4: 10u; C0805
C5: 1n; C1206
CC-BY-SA1: CC-BY-SA_LOGO
D1: PRTR5V0U2X; SOT143B
DRILEGEND: DRILEGEND
J1, J2: MH10-1; MH10-1-0.1
J3: USB_AF-006
L1: BLM31PG601SN1L; FB1206
R1: 33R; R0402
R2: 100k; R0402
R3, R5, R6: 0R; R0402
R4: 15k; R0402
S1: DOMINO_LOGO
U1: MP65151DJ; SOT23-6
U$1: ROHS_LOGO
U$3: A5L-LOC
U$4, U$10: DOMINO_LOGO_SMALL
U$5: CE_LOGO_SMALL
U$6: FCC_LOGO_SMALL
U$8: RECYCLE_BIN_LOGO
U$11: ESD_LOGO

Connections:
+5V: C1.1, J2.7, R2.2, U1.1
DP_PWR: C2.1, L1.1, U1.6
D_N: D1.2, J3.2, R5.1
D_P: D1.3, J3.3, R6.1
EN: R1.1, R2.1, R3.2, U1.3
GND: C1.2, C2.2, C3.2, C4.2, C5.2, D1.1, J1.10, J2.6, J2.10, J3.4, R4.2, U1.2
ILIM: R4.1, U1.5
JTAG_TDI: J1.3, R1.2
unnamed: R3.1, U1.4
PE: C5.1, J3.S$1, J3.S$2
USB_N: J2.8, R5.2
USB_P: J2.9, R6.2
VBUS: C3.1, C4.1, D1.4, J3.1, L1.2

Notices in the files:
Others/Domino Pi No Teardrop.sch:
© 2014, Michel Stempin
All rights reserved.
parts and their libraries:
Domino: See creativecommons.org/licenses/by-sa/4.0/ for details.
Domino: See creativecommons.org/licenses/by-sa/3.0/ for details.
Domino: Copyright © 2012, Michel Stempin, All rights reserved
Licenced under Creative Commons CC BY-SA 3.0 license.
